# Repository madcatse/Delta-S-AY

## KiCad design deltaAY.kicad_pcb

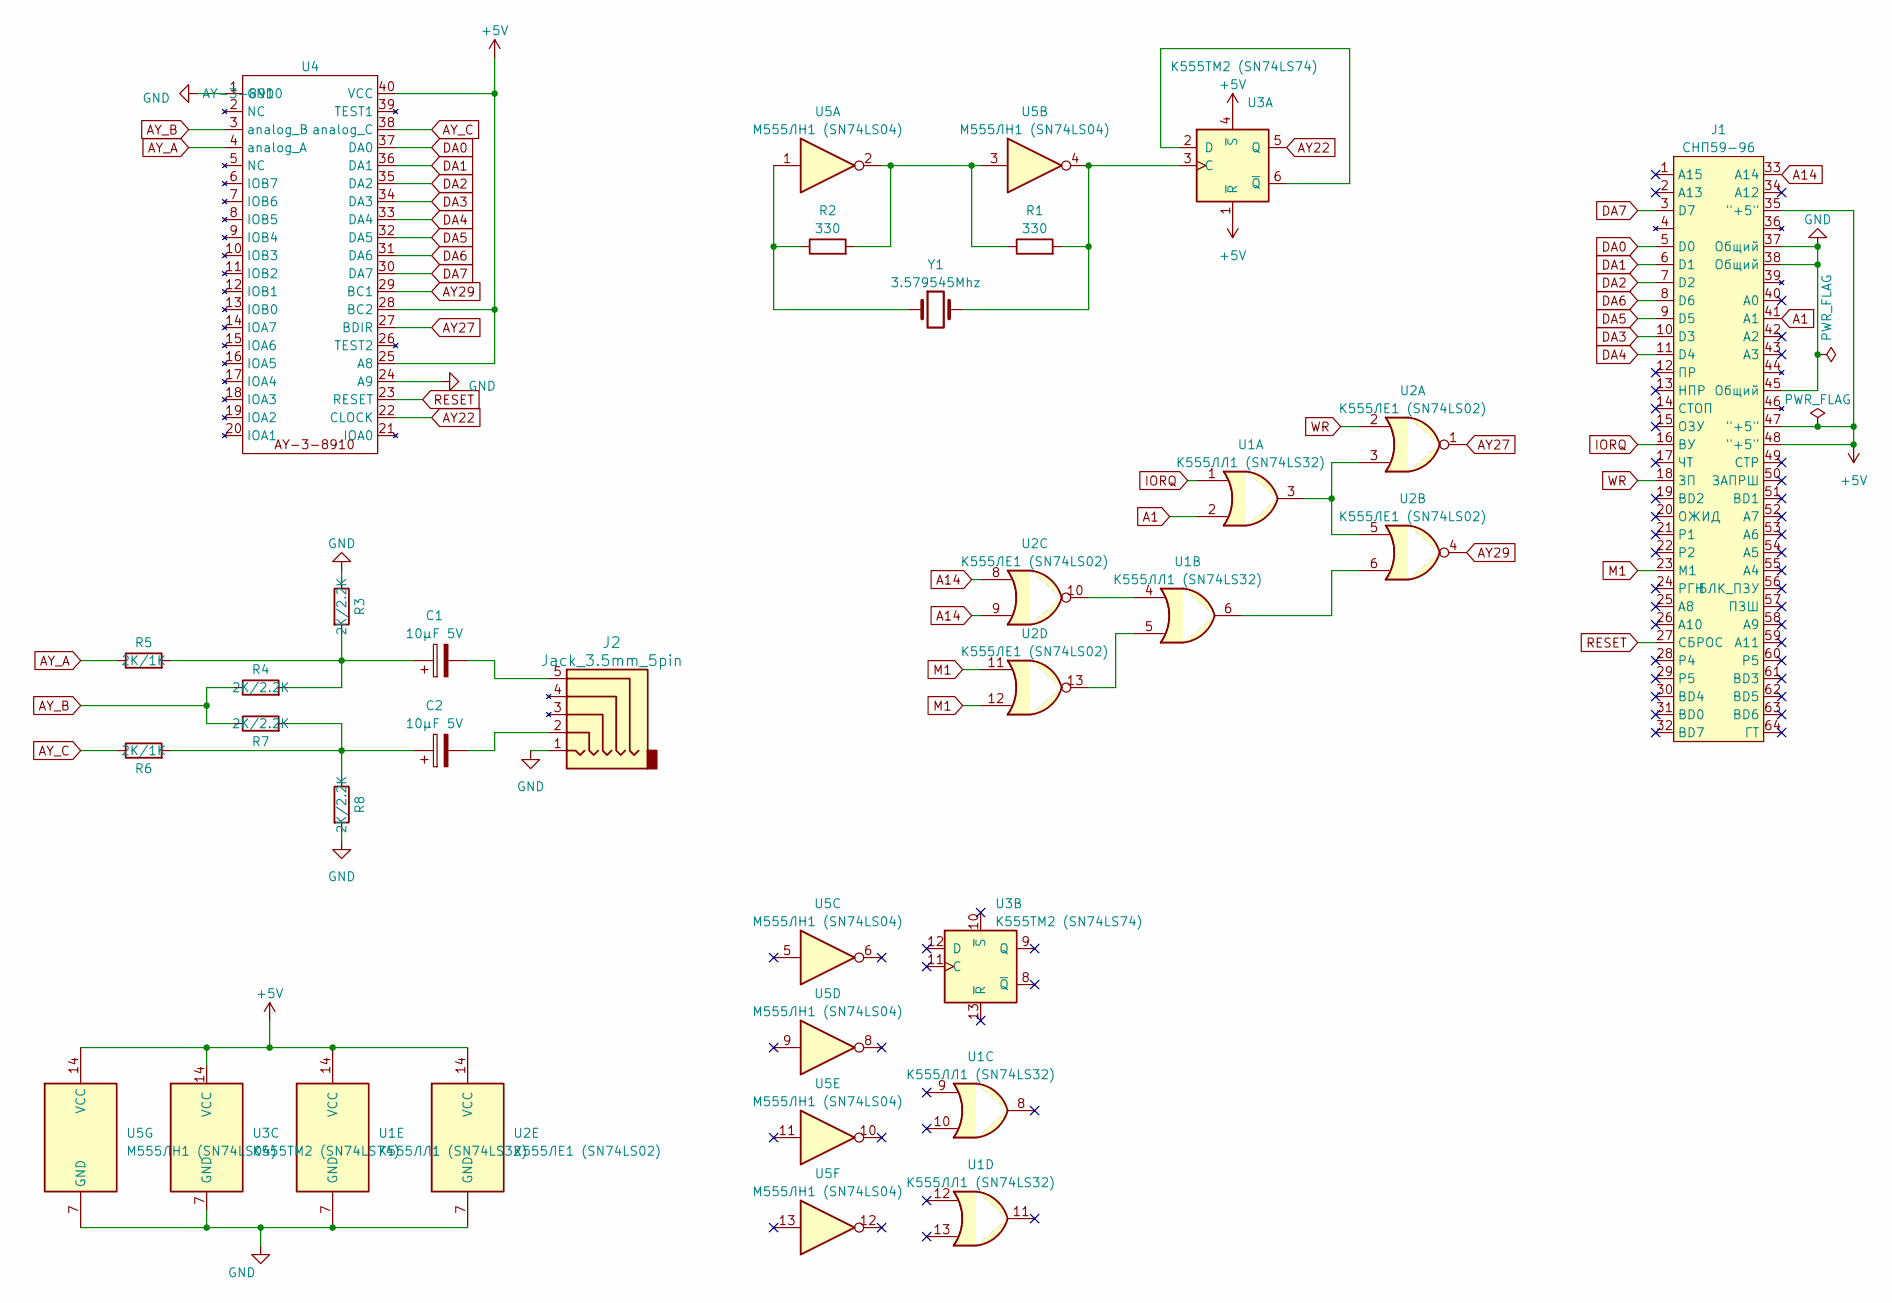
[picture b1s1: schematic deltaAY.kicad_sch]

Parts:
C1, C2: 10μF 5V; CP_Radial_D8.0mm_P3.80mm
J1: СНП59-96; SNP96
J2: Jack_3.5mm_5pin; jack_5_pin_3f07_FINAL
R1, R2: 330; R_Axial_DIN0207_L6.3mm_D2.5mm_P7.62mm_Horizontal
R3, R4, R7, R8: 2K/2.2K; R_Axial_DIN0207_L6.3mm_D2.5mm_P7.62mm_Horizontal
R5, R6: 2K/1K; R_Axial_DIN0207_L6.3mm_D2.5mm_P7.62mm_Horizontal
U1: К555ЛЛ1 (SN74LS32); DIP-14_W7.62mm_LongPads
U2: К555ЛЕ1 (SN74LS02); DIP-14_W7.62mm_LongPads
U3: К555ТМ2 (SN74LS74); DIP-14_W7.62mm_LongPads
U4: AY-3-8910; DIP-40_W15.24mm_LongPads
U5: М555ЛН1 (SN74LS04); DIP-14_W7.62mm_LongPads
Y1: 3.579545Mhz; Crystal_HC49-U_Horizontal

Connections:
+5V: J1.35 ("+5"), J1.47 ("+5"), J1.48 ("+5"), U1.14 (VCC), U2.14 (VCC), U3.1 (~R), U3.4 (~S), U3.14 (VCC), U4.25 (A8), U4.28 (BC2), U4.40 (VCC), U5.14 (VCC)
A1: J1.41 (A1), U1.2
A14: J1.33 (A14), U2.8, U2.9
AY22: U3.5 (Q), U4.22 (CLOCK)
AY27: U2.1, U4.27 (BDIR)
AY29: U2.4, U4.29 (BC1)
AY_A: R5.1, U4.4 (analog_A)
AY_B: R4.1, R7.1, U4.3 (analog_B)
AY_C: R6.1, U4.38 (analog_C)
DA0: J1.5 (D0), U4.37 (DA0)
DA1: J1.6 (D1), U4.36 (DA1)
DA2: J1.7 (D2), U4.35 (DA2)
DA3: J1.10 (D3), U4.34 (DA3)
DA4: J1.11 (D4), U4.33 (DA4)
DA5: J1.9 (D5), U4.32 (DA5)
DA6: J1.8 (D6), U4.31 (DA6)
DA7: J1.3 (D7), U4.30 (DA7)
GND: J1.37 (Общий), J1.38 (Общий), J1.45 (Общий), J2.1, R3.1, R8.2, U1.7 (GND), U2.7 (GND), U3.7 (GND), U4.1 (GND), U4.24 (A9), U5.7 (GND)
IORQ: J1.16 (ВУ), U1.1
M1: J1.23 (М1), U2.11, U2.12
unnamed: C1.1, R3.2, R4.2, R5.2
unnamed: C1.2, J2.5
unnamed: C2.1, R6.2, R7.2, R8.1
unnamed: C2.2, J2.2
unnamed: R1.1, R2.2, U5.2, U5.3
unnamed: R2.1, U5.1, Y1.1
unnamed: U1.3, U2.3, U2.5
unnamed: U1.4, U2.10
unnamed: U1.5, U2.13
unnamed: U1.6, U2.6
unnamed: R1.2, U3.3 (C), U5.4, Y1.2
unnamed: U3.2 (D), U3.6 (~Q)
RESET: J1.27 (СБРОС), U4.23 (RESET)
WR: J1.18 (ЗП), U2.2

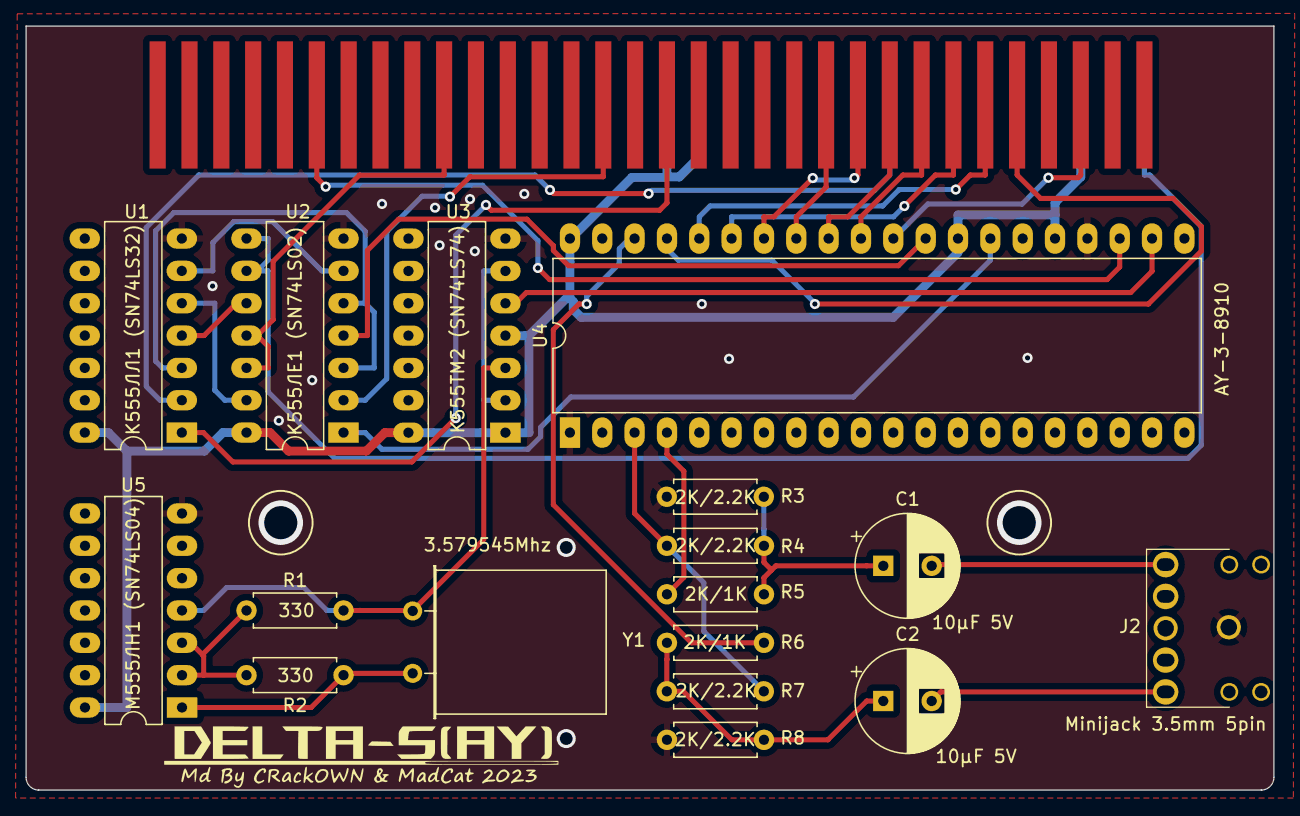
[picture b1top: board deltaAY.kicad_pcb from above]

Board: 2 copper layers, 98.0 x 60.0 mm, 18 parts (0 on the bottom side), 34 nets.

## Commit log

2023-05-30 initial
2023-05-31 31052023
2023-05-31 31 may 2023
2023-07-18 Update 19072023
2023-07-19 Release ver1 19-07-2023
    First release
